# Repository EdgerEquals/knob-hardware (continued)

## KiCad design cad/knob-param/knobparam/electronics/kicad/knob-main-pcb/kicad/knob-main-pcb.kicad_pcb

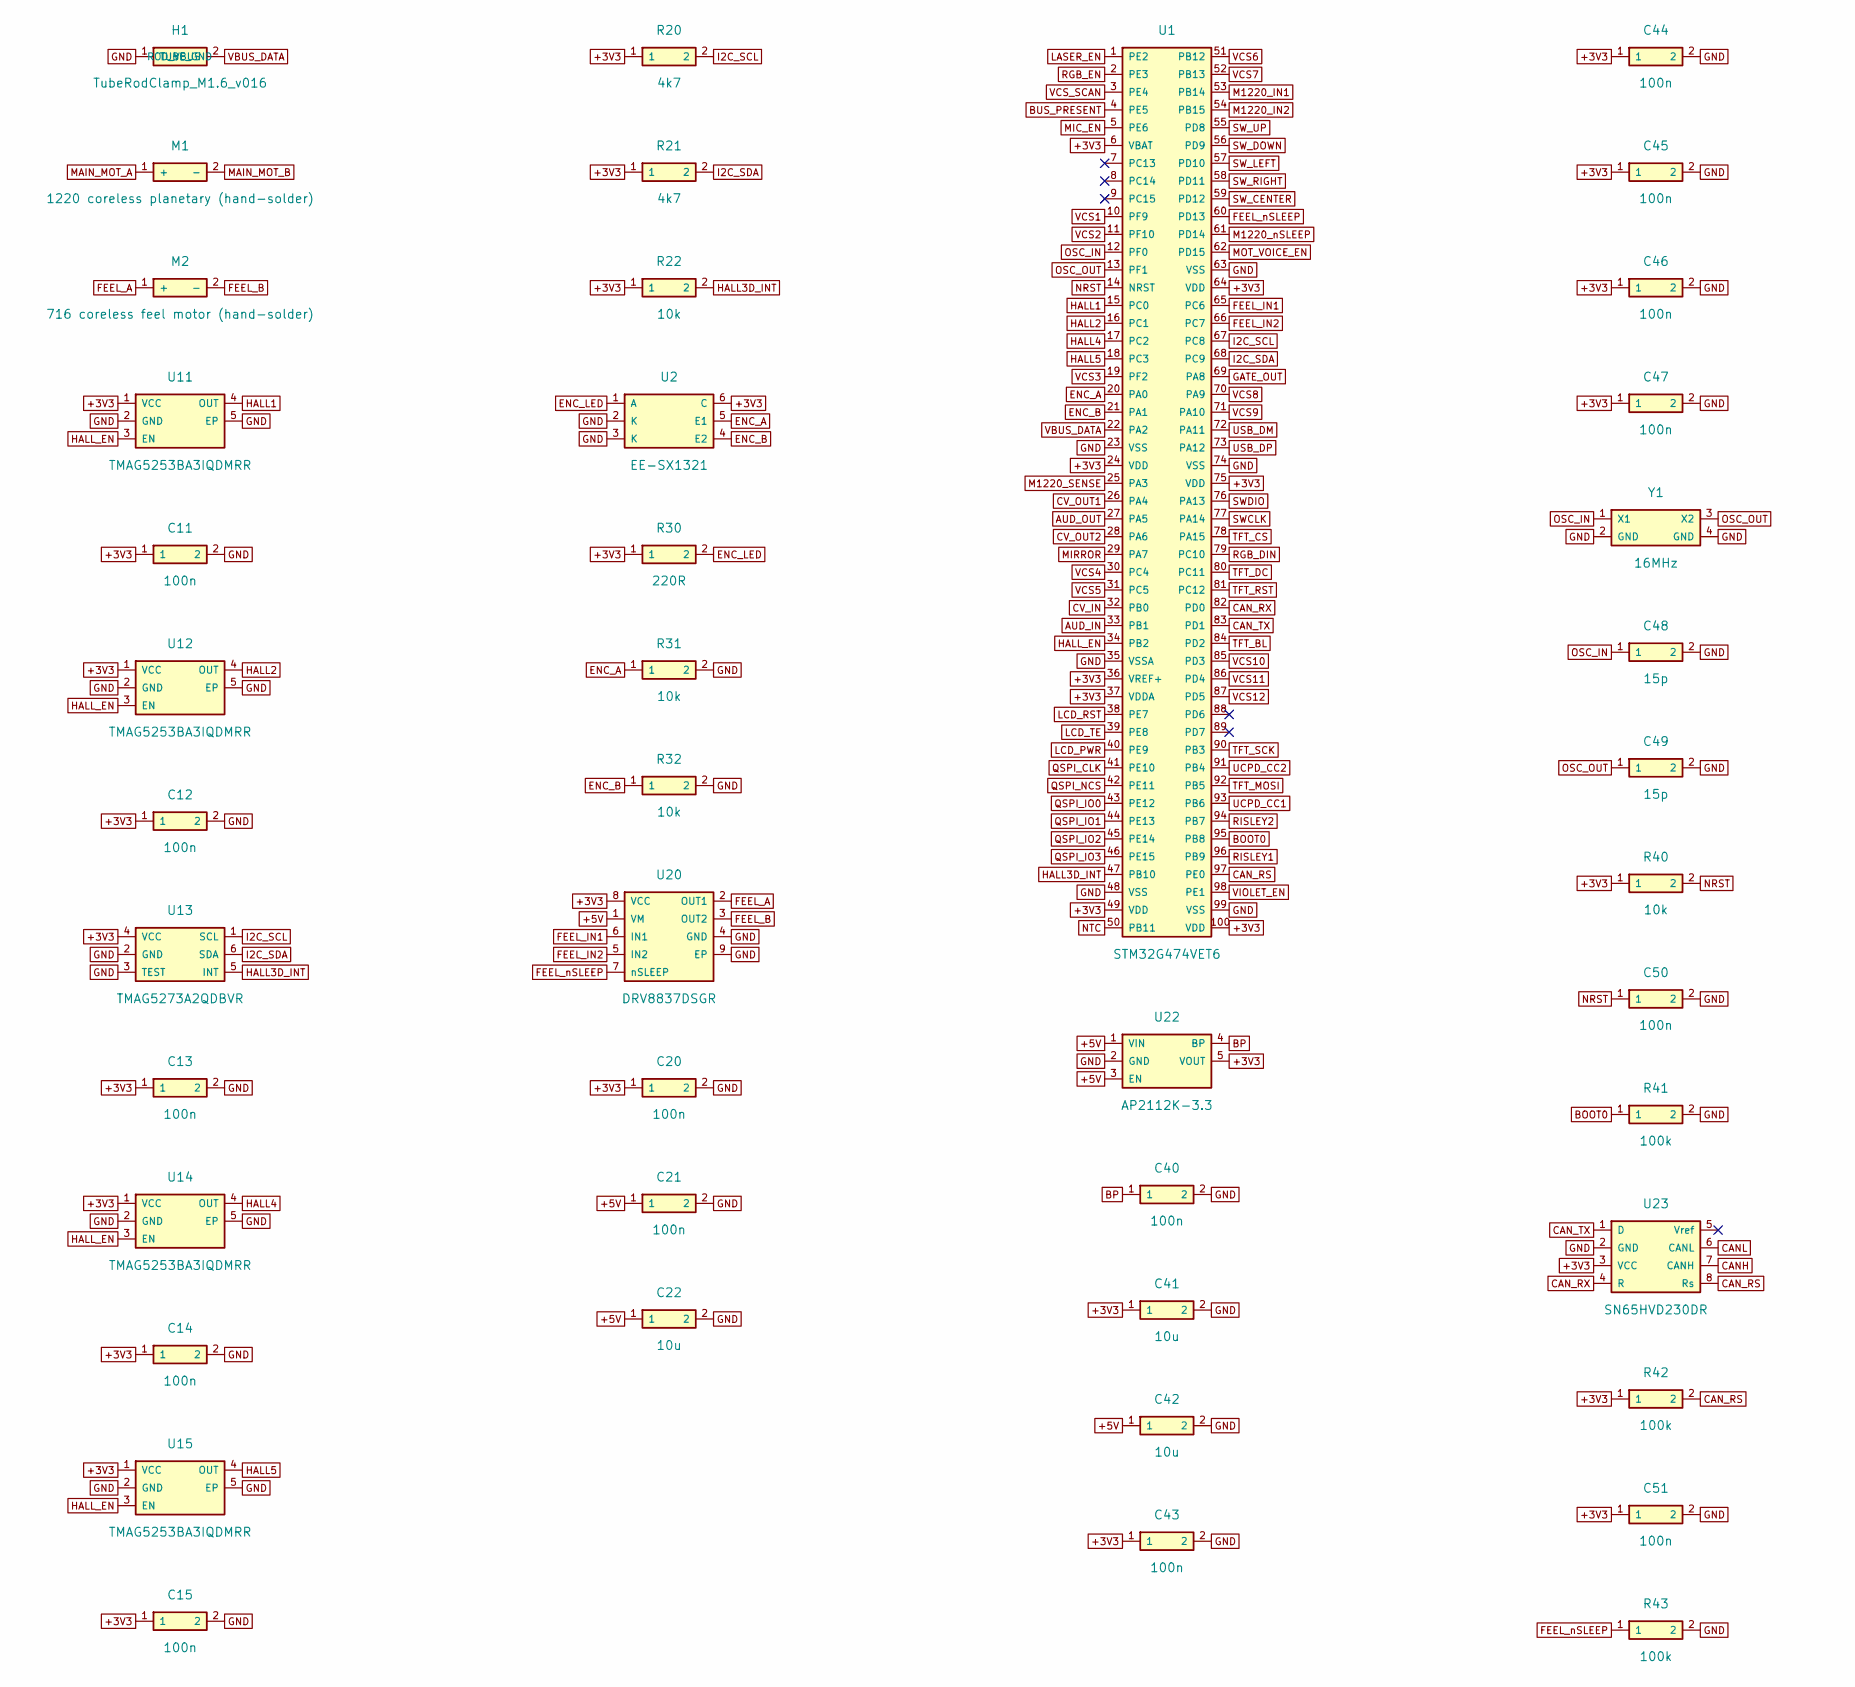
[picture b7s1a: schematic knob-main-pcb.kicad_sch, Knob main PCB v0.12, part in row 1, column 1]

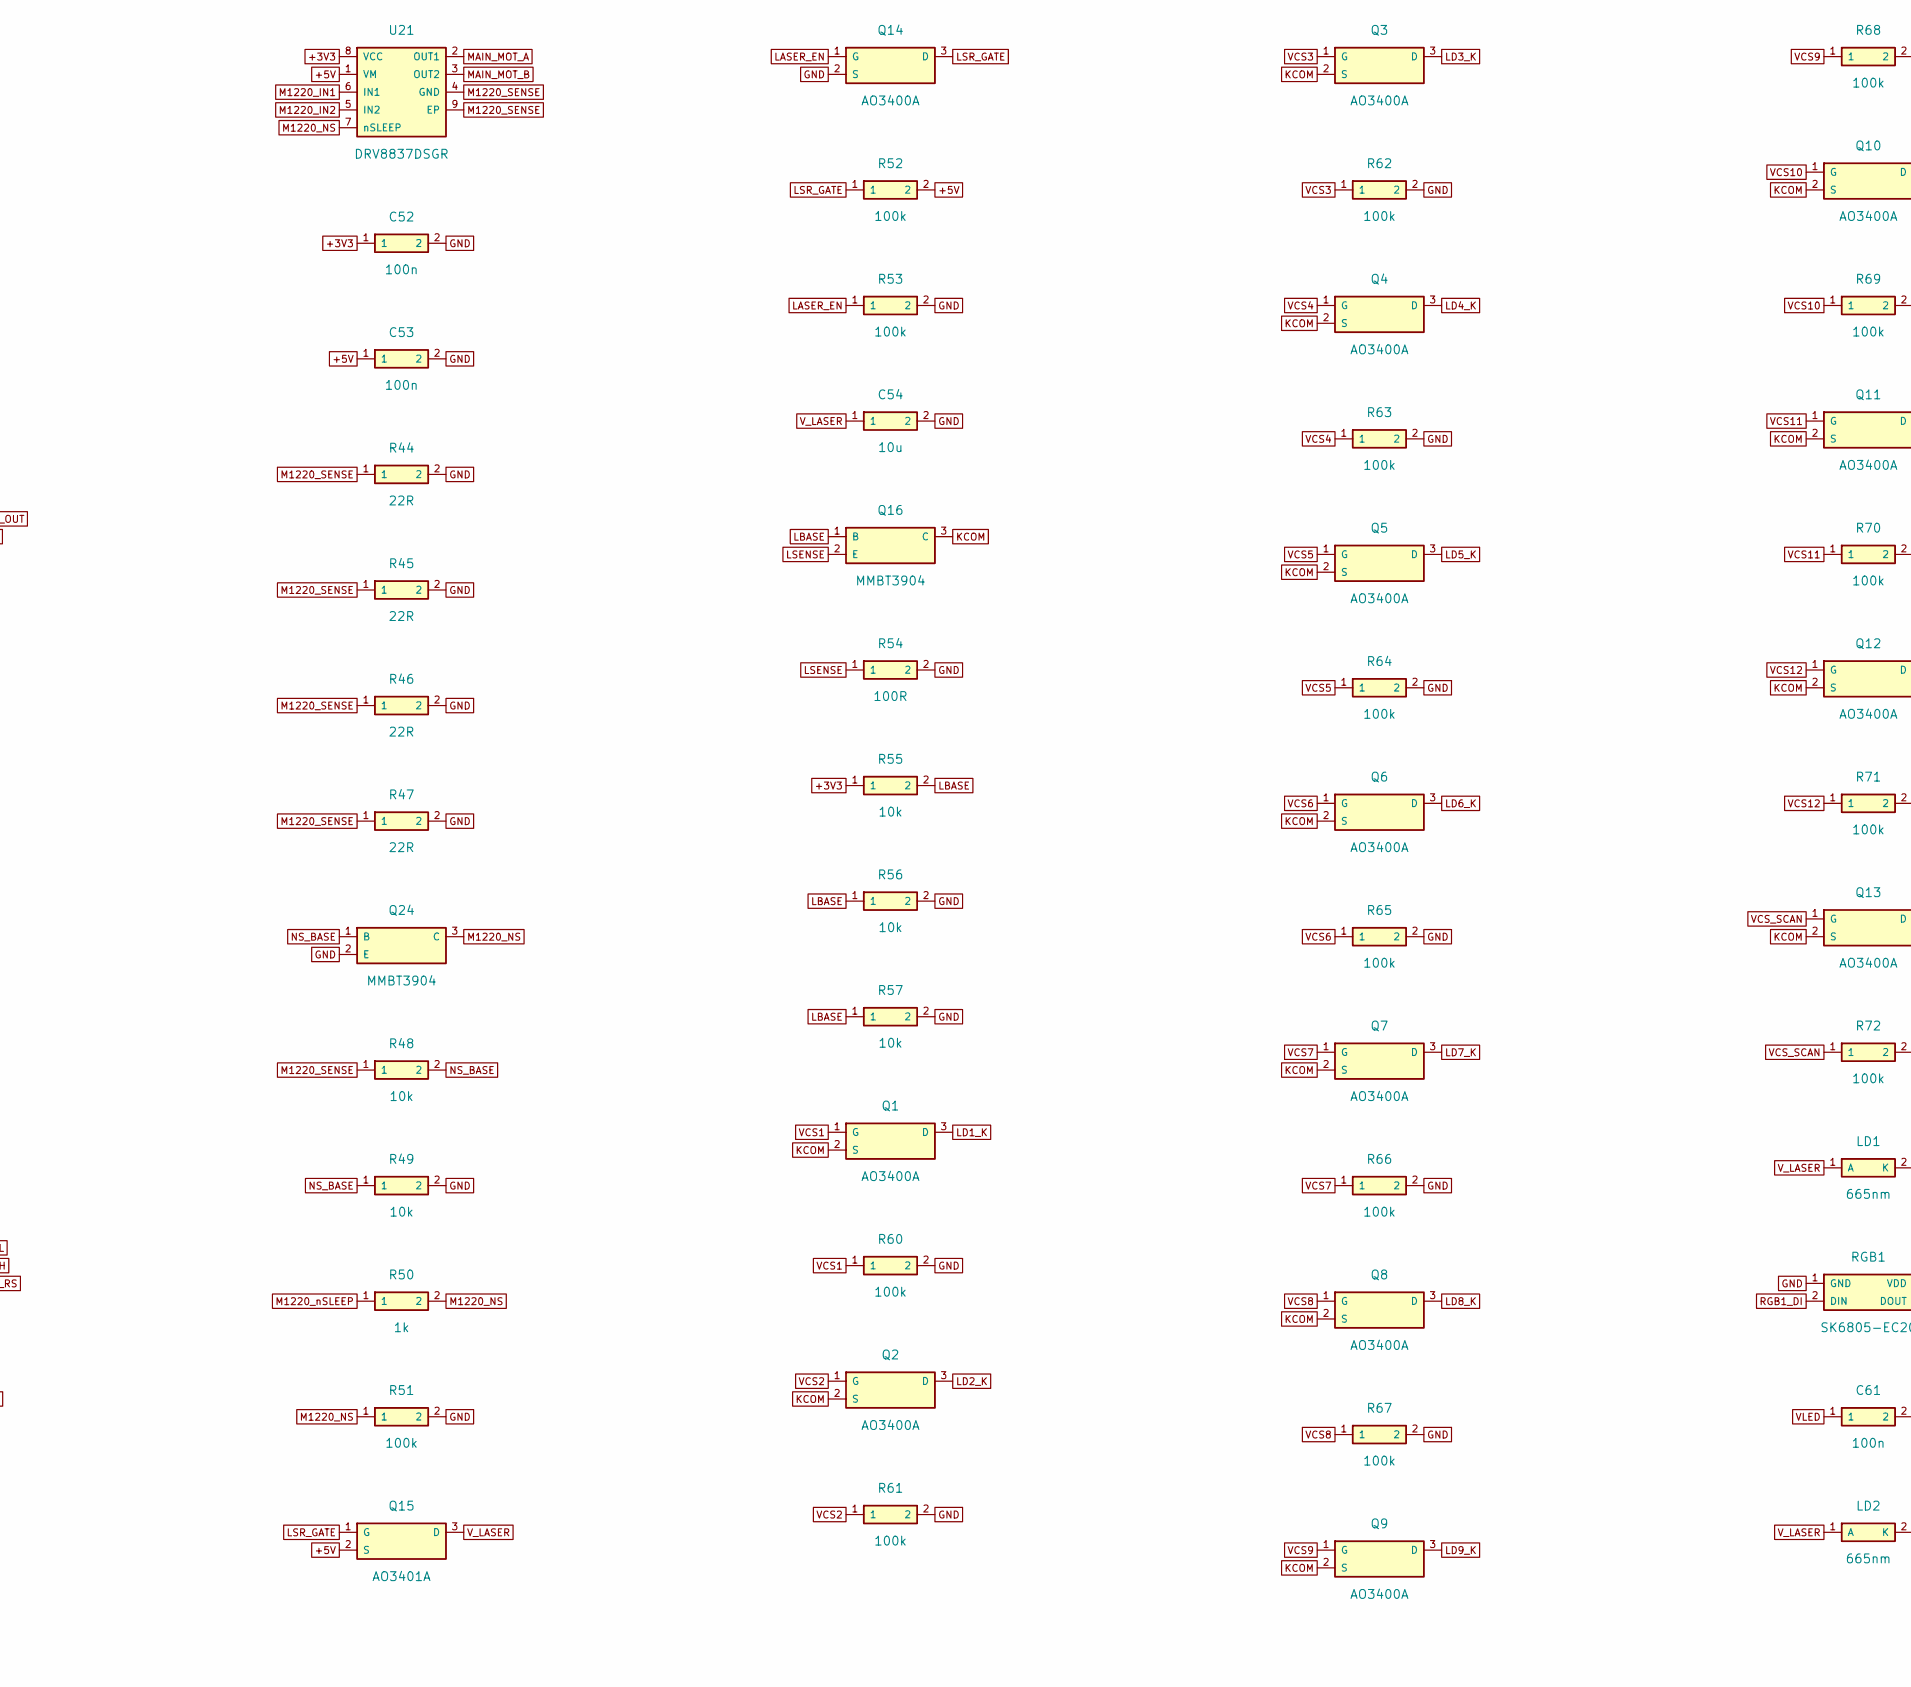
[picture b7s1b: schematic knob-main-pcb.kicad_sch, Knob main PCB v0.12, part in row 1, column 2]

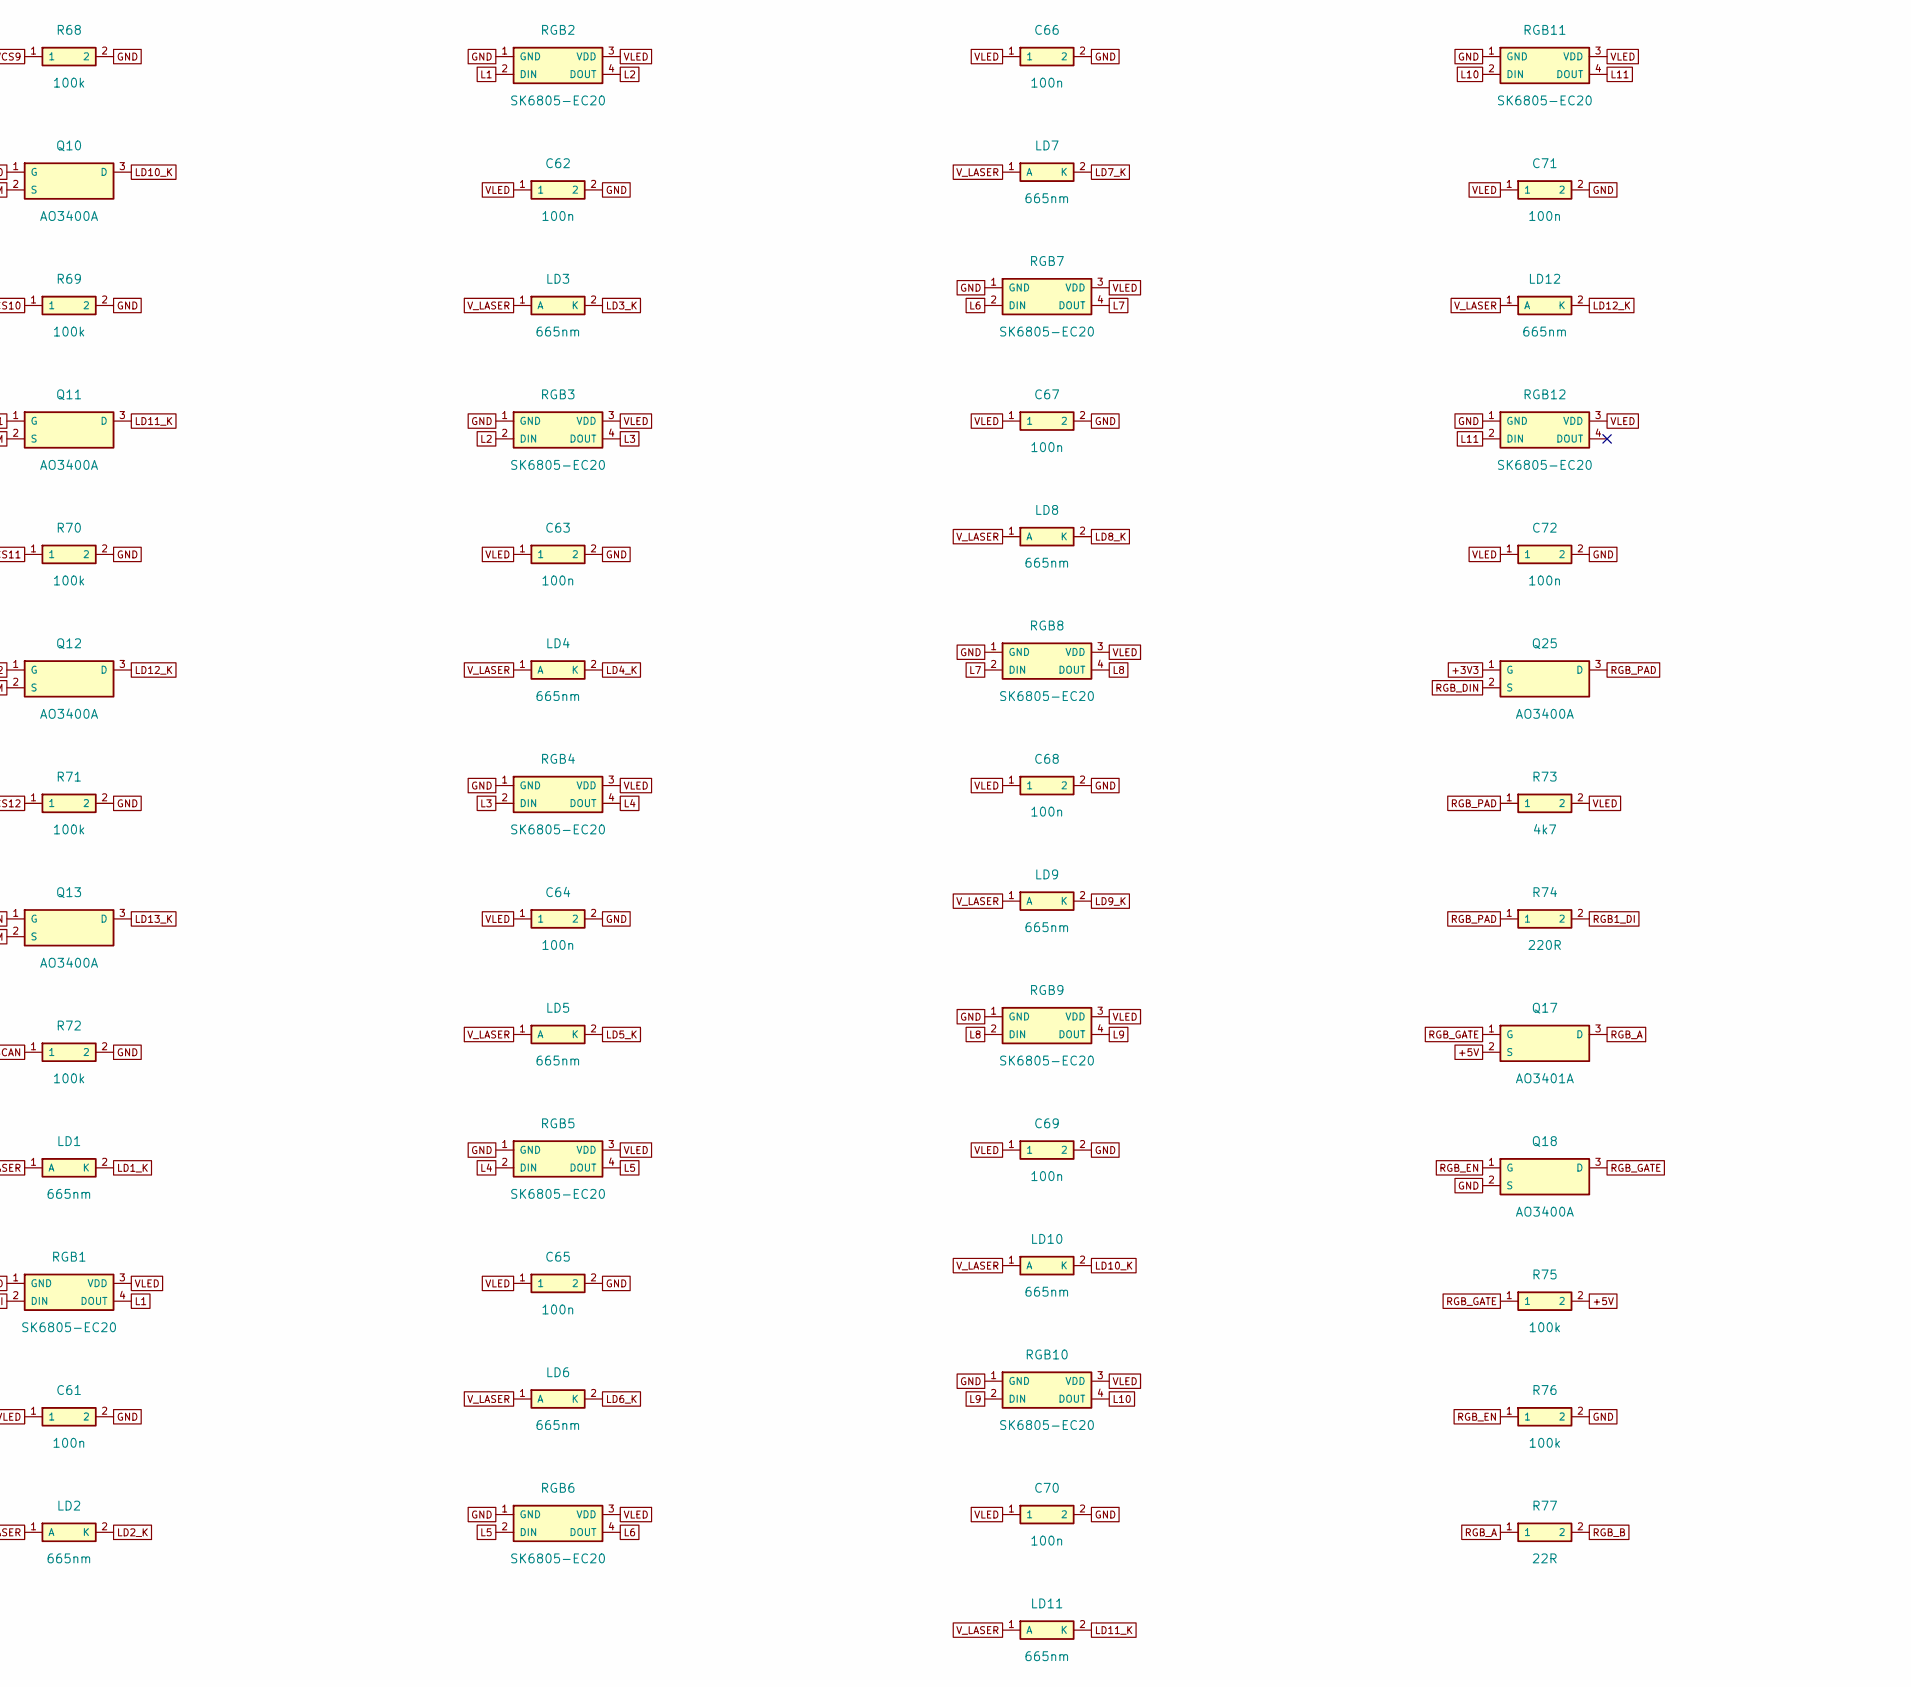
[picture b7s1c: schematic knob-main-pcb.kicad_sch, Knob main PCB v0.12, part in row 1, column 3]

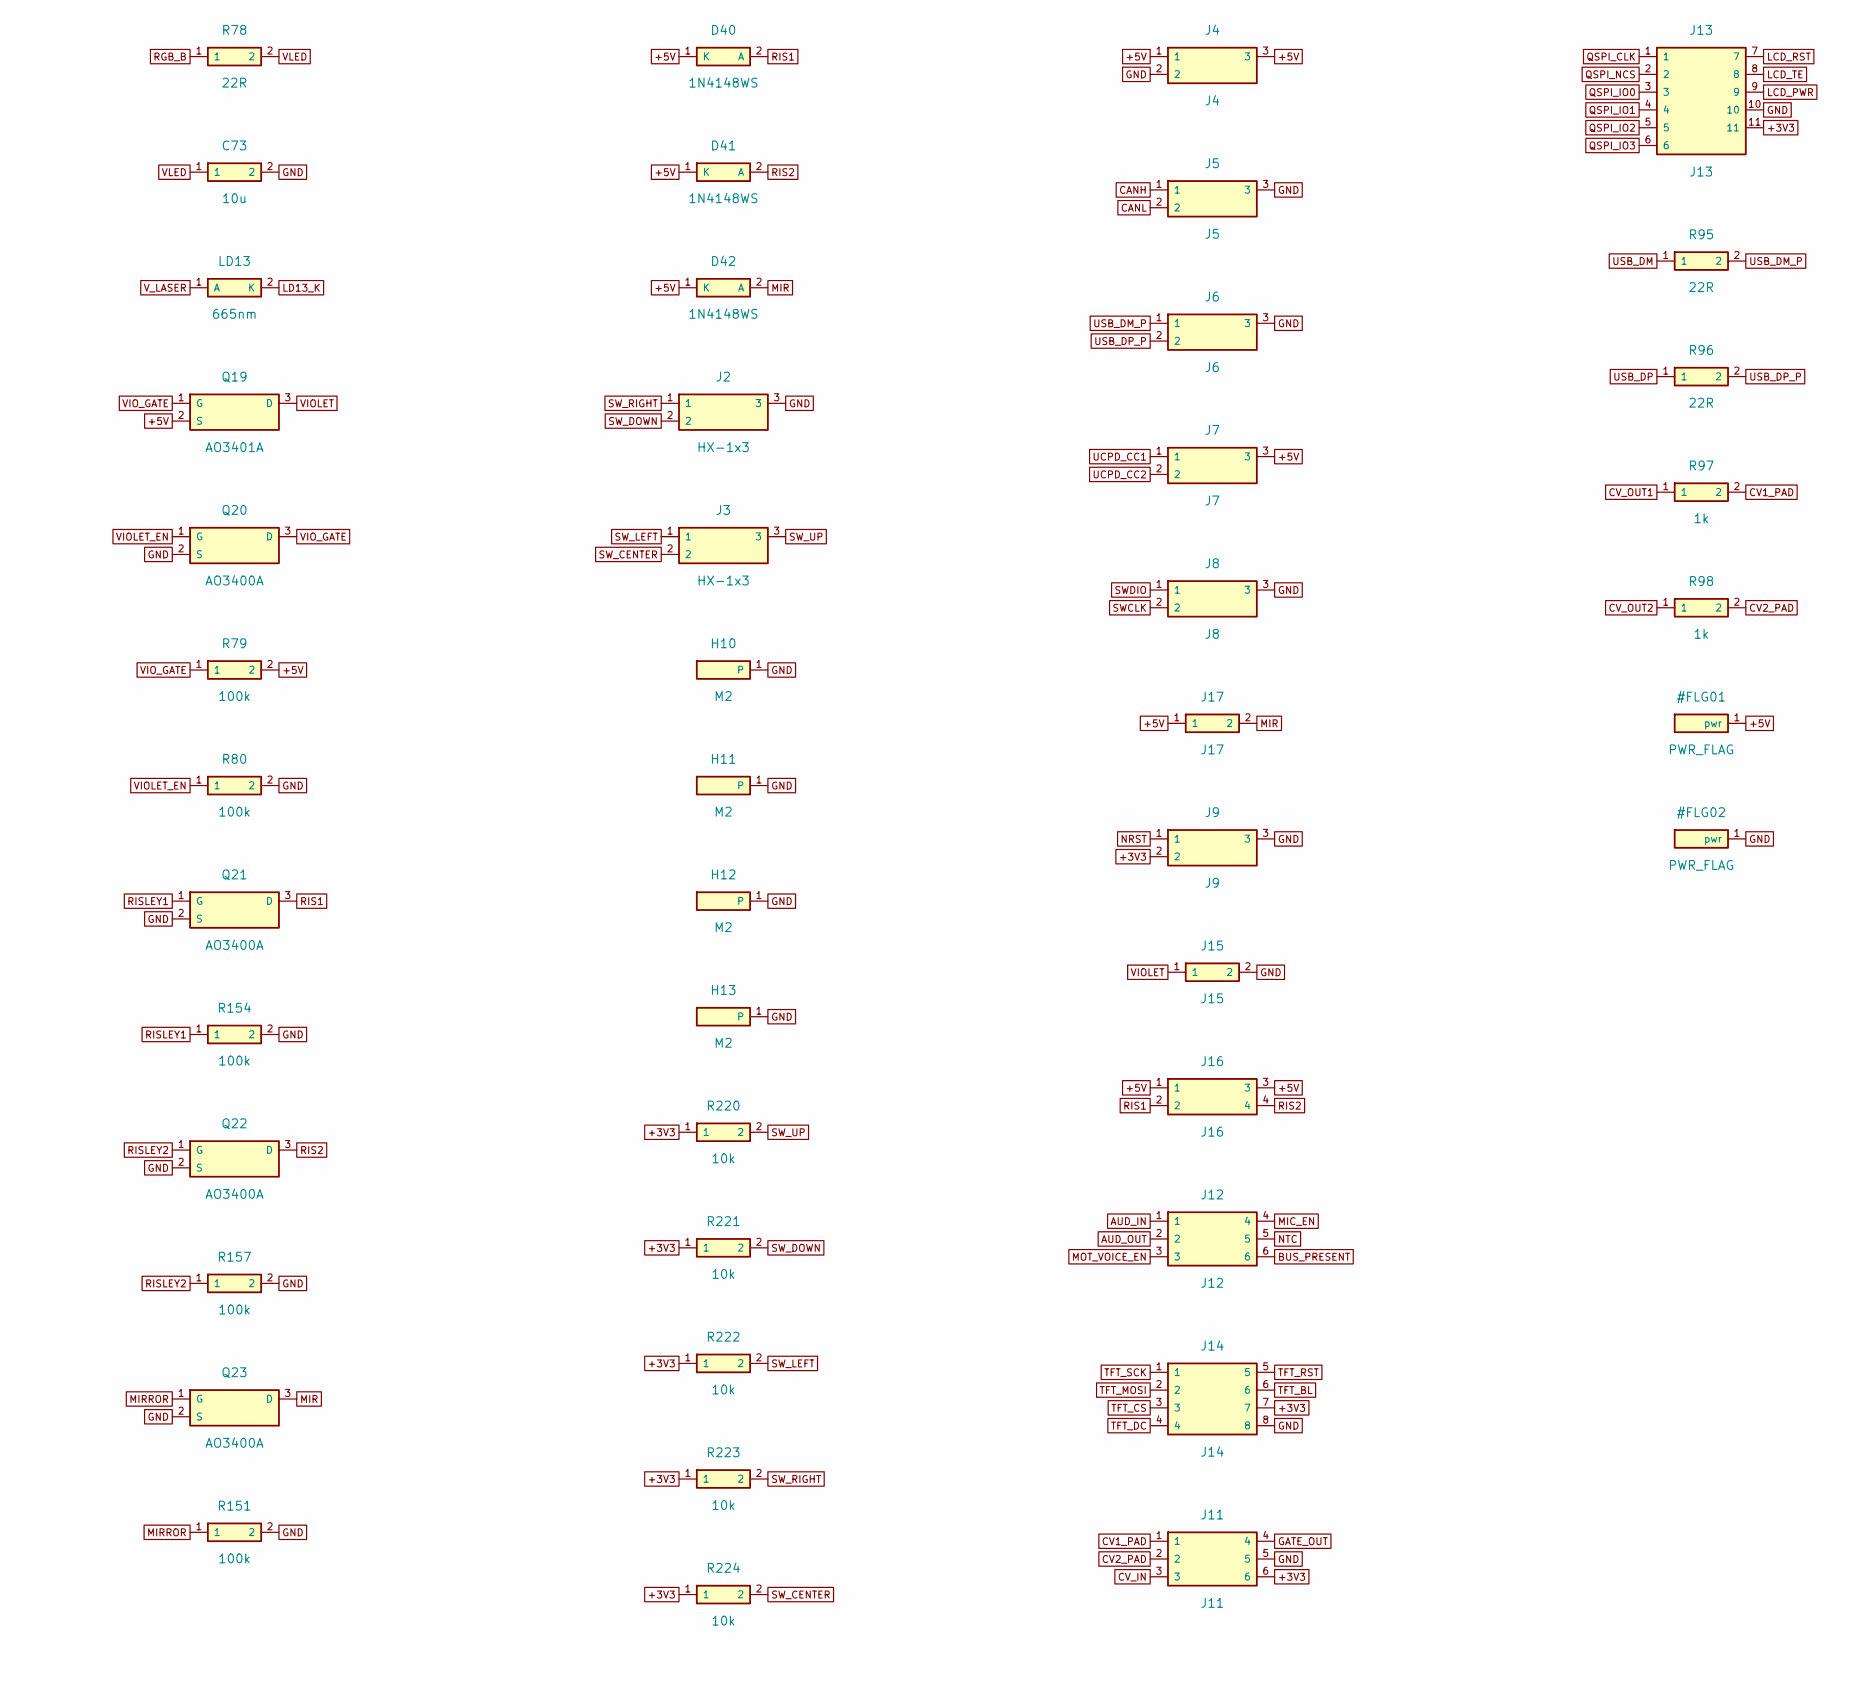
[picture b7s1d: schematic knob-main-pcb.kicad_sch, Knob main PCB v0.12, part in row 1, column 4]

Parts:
C11, C12, C13, C14, C15, C20, C21, C40, C43, C44, C45, C46, C47, C50, C51, C52, C53, C61, C62, C63, C64, C65, C66, C67, C68, C69, C70, C71, C72: 100n; C_0402; MPN CL05B104KO5NNNC; LCSC C1525
C22, C41, C42, C54, C73: 10u; C_0603; MPN CL10A106KP8NNNC; LCSC C19702
C48, C49: 15p; C_0402; MPN 0402CG150J500NT; LCSC C1548
D40, D41, D42: 1N4148WS; D_SOD-323; MPN 1N4148WS; LCSC C2128
H1: TubeRodClamp_M1.6_v016; TubeRodClamp_Main_M1.6_v016
H10, H11, H12, H13: M2; Mount_M2_PTH
J2, J3: HX-1x3; PinSocket_1x03_P2.54; MPN HX PM2.54-1x3P ZC H11; LCSC C41427518
J4: J4; PadRow_1x03
J5: J5; PadRow_1x03
J6: J6; PadRow_1x03
J7: J7; PadRow_1x03
J8: J8; PadRow_1x03
J9: J9; PadRow_1x03
J11: J11; PadRow_1x06
J12: J12; PadRow_1x06
J13: J13; PadRow_1x11
J14: J14; PadRow_1x08
J15: J15; PadRow_1x02
J16: J16; PadRow_1x04
J17: J17; PadRow_1x02
LD1, LD2, LD3, LD4, LD5, LD6, LD7, LD8, LD9, LD10, LD11, LD12, LD13: 665nm; LED_2835_VCSEL; MPN JNJ-V-2835CW-665003-S-D1; LCSC C42375664
M1: 1220 coreless planetary (hand-solder); Motor_1220_Tabs_Relief
M2: 716 coreless feel motor (hand-solder); FeelMotor_716_LeadPads
Q1, Q2, Q3, Q4, Q5, Q6, Q7, Q8, Q9, Q10, Q11, Q12, Q13, Q14, Q18, Q20, Q21, Q22, Q23, Q25: AO3400A; SOT-23; MPN AO3400A; LCSC C20917
Q15, Q17, Q19: AO3401A; SOT-23; MPN AO3401A; LCSC C15127
Q16, Q24: MMBT3904; SOT-23; MPN MMBT3904; LCSC C20526
R20, R21, R73: 4k7; R_0402; MPN 0402WGF4701TCE; LCSC C25900
R22, R31, R32, R40, R48, R49, R55, R56, R57, R220, R221, R222, R223, R224: 10k; R_0402; MPN RC0402FR-0710KL; LCSC C60490
R30, R74: 220R; R_0402; MPN 0402WGF2200TCE; LCSC C25091
R41, R42, R43, R51, R52, R53, R60, R61, R62, R63, R64, R65, R66, R67, R68, R69, R70, R71, R72, R75, R76, R79, R80, R151, R154, R157: 100k; R_0402; MPN 0402WGF1003TCE; LCSC C25741
R44, R45, R46, R47, R77, R78, R95, R96: 22R; R_0402; MPN 0402WGF220KTCE; LCSC C25101
R50, R97, R98: 1k; R_0402; MPN 0402WGF1001TCE; LCSC C11702
R54: 100R; R_0603; MPN 0603WAF1000T5E; LCSC C22775
RGB1, RGB2, RGB3, RGB4, RGB5, RGB6, RGB7, RGB8, RGB9, RGB10, RGB11, RGB12: SK6805-EC20; LED_SK6805_EC20; MPN SK6805-EC20; LCSC C2890036
U1: STM32G474VET6; LQFP-100_14x14mm_P0.5mm; MPN STM32G474VET6; LCSC C431632
U2: EE-SX1321; Omron_EE-SX1321; MPN EE-SX1321; LCSC C469128
U11, U12, U14, U15: TMAG5253BA3IQDMRR; X2SON-4_TMAG5253; MPN TMAG5253BA3IQDMRR; LCSC C22401868
U13: TMAG5273A2QDBVR; SOT-23-6_TMAG5273_Tight; MPN TMAG5273A2QDBVR; LCSC C3715882
U20, U21: DRV8837DSGR; WSON-8_2x2_DRV8837; MPN DRV8837DSGR; LCSC C39159
U22: AP2112K-3.3; SOT-23-5; MPN AP2112K-3.3TRG1; LCSC C51118
U23: SN65HVD230DR; SOIC-8_3.9x4.9mm_P1.27mm; MPN SN65HVD230DR; LCSC C12084
Y1: 16MHz; Crystal_3225; MPN X322516MLB4SI; LCSC C13738

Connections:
+3V3: C11.1, C12.1, C13.1, C14.1, C15.1, C20.1, C41.1, C43.1, C44.1, C45.1, C46.1, C47.1, C51.1, C52.1, J9.2, J11.6, J13.11, J14.7, Q25.1 (G), R20.1, R21.1, R22.1, R30.1, R40.1, R42.1, R55.1, R220.1, R221.1, R222.1, R223.1, R224.1, U1.6 (VBAT), U1.24 (VDD), U1.36 (VREF+), U1.37 (VDDA), U1.49 (VDD), U1.64 (VDD), U1.75 (VDD), U1.100 (VDD), U2.6 (C), U11.1 (VCC), U12.1 (VCC), U13.4 (VCC), U14.1 (VCC), U15.1 (VCC), U20.8 (VCC), U21.8 (VCC), U22.5 (VOUT), U23.3 (VCC)
+5V: C21.1, C22.1, C42.1, C53.1, D40.1 (K), D41.1 (K), D42.1 (K), J4.1, J4.3, J7.3, J16.1, J16.3, J17.1, Q15.2 (S), Q17.2 (S), Q19.2 (S), R52.2, R75.2, R79.2, U20.1 (VM), U21.1 (VM), U22.1 (VIN), U22.3 (EN)
AUD_IN: J12.1, U1.33 (PB1)
AUD_OUT: J12.2, U1.27 (PA5)
BOOT0: R41.1, U1.95 (PB8)
BP: C40.1, U22.4 (BP)
BUS_PRESENT: J12.6, U1.4 (PE5)
CANH: J5.1, U23.7 (CANH)
CANL: J5.2, U23.6 (CANL)
CAN_RS: R42.2, U1.97 (PE0), U23.8 (Rs)
CAN_RX: U1.82 (PD0), U23.4 (R)
CAN_TX: U1.83 (PD1), U23.1 (D)
CV1_PAD: J11.1, R97.2
CV2_PAD: J11.2, R98.2
CV_IN: J11.3, U1.32 (PB0)
CV_OUT1: R97.1, U1.26 (PA4)
CV_OUT2: R98.1, U1.28 (PA6)
ENC_A: R31.1, U1.20 (PA0), U2.5 (E1)
ENC_B: R32.1, U1.21 (PA1), U2.4 (E2)
ENC_LED: R30.2, U2.1 (A)
FEEL_A: M2.1 (+), U20.2 (OUT1)
FEEL_B: M2.2 (-), U20.3 (OUT2)
FEEL_IN1: U1.65 (PC6), U20.6 (IN1)
FEEL_IN2: U1.66 (PC7), U20.5 (IN2)
FEEL_nSLEEP: R43.1, U1.60 (PD13), U20.7 (nSLEEP)
GATE_OUT: J11.4, U1.69 (PA8)
GND: C11.2, C12.2, C13.2, C14.2, C15.2, C20.2, C21.2, C22.2, C40.2, C41.2, C42.2, C43.2, C44.2, C45.2, C46.2, C47.2, C48.2, C49.2, C50.2, C51.2, C52.2, C53.2, C54.2, C61.2, C62.2, C63.2, C64.2, C65.2, C66.2, C67.2, C68.2, C69.2, C70.2, C71.2, C72.2, C73.2, H1.1 (TUBE_GND), H10.1, H11.1, H12.1, H13.1, J2.3, J4.2, J5.3, J6.3, J8.3, J9.3, J11.5, J13.10, J14.8, J15.2, Q14.2 (S), Q18.2 (S), Q20.2 (S), Q21.2 (S), Q22.2 (S), Q23.2 (S), Q24.2 (E), R31.2, R32.2, R41.2, R43.2, R44.2, R45.2, R46.2, R47.2, R49.2, R51.2, R53.2, R54.2, R56.2, R57.2, R60.2, R61.2, R62.2, R63.2, R64.2, R65.2, R66.2, R67.2, R68.2, R69.2, R70.2, R71.2, R72.2, R76.2, R80.2, R151.2, R154.2, R157.2, RGB1.1 (GND), RGB2.1 (GND), RGB3.1 (GND), RGB4.1 (GND), RGB5.1 (GND), RGB6.1 (GND), RGB7.1 (GND), RGB8.1 (GND), RGB9.1 (GND), RGB10.1 (GND), RGB11.1 (GND), RGB12.1 (GND), U1.23 (VSS), U1.35 (VSSA), U1.48 (VSS), U1.63 (VSS), U1.74 (VSS), U1.99 (VSS), U2.2 (K), U2.3 (K), U11.2 (GND), U11.5 (EP), U12.2 (GND), U12.5 (EP), U13.2 (GND), U13.3 (TEST), U14.2 (GND), U14.5 (EP), U15.2 (GND), U15.5 (EP), U20.4 (GND), U20.9 (EP), U22.2 (GND), U23.2 (GND), Y1.2 (GND), Y1.4 (GND)
HALL1: U1.15 (PC0), U11.4 (OUT)
HALL2: U1.16 (PC1), U12.4 (OUT)
HALL3D_INT: R22.2, U1.47 (PB10), U13.5 (INT)
HALL4: U1.17 (PC2), U14.4 (OUT)
HALL5: U1.18 (PC3), U15.4 (OUT)
HALL_EN: U1.34 (PB2), U11.3 (EN), U12.3 (EN), U14.3 (EN), U15.3 (EN)
I2C_SCL: R20.2, U1.67 (PC8), U13.1 (SCL)
I2C_SDA: R21.2, U1.68 (PC9), U13.6 (SDA)
KCOM: Q1.2 (S), Q2.2 (S), Q3.2 (S), Q4.2 (S), Q5.2 (S), Q6.2 (S), Q7.2 (S), Q8.2 (S), Q9.2 (S), Q10.2 (S), Q11.2 (S), Q12.2 (S), Q13.2 (S), Q16.3 (C)
L1: RGB1.4 (DOUT), RGB2.2 (DIN)
L2: RGB2.4 (DOUT), RGB3.2 (DIN)
L3: RGB3.4 (DOUT), RGB4.2 (DIN)
L4: RGB4.4 (DOUT), RGB5.2 (DIN)
L5: RGB5.4 (DOUT), RGB6.2 (DIN)
L6: RGB6.4 (DOUT), RGB7.2 (DIN)
L7: RGB7.4 (DOUT), RGB8.2 (DIN)
L8: RGB8.4 (DOUT), RGB9.2 (DIN)
L9: RGB9.4 (DOUT), RGB10.2 (DIN)
L10: RGB10.4 (DOUT), RGB11.2 (DIN)
L11: RGB11.4 (DOUT), RGB12.2 (DIN)
LASER_EN: Q14.1 (G), R53.1, U1.1 (PE2)
LBASE: Q16.1 (B), R55.2, R56.1, R57.1
LCD_PWR: J13.9, U1.40 (PE9)
LCD_RST: J13.7, U1.38 (PE7)
LCD_TE: J13.8, U1.39 (PE8)
LD1_K: LD1.2 (K), Q1.3 (D)
LD2_K: LD2.2 (K), Q2.3 (D)
LD3_K: LD3.2 (K), Q3.3 (D)
LD4_K: LD4.2 (K), Q4.3 (D)
LD5_K: LD5.2 (K), Q5.3 (D)
LD6_K: LD6.2 (K), Q6.3 (D)
LD7_K: LD7.2 (K), Q7.3 (D)
LD8_K: LD8.2 (K), Q8.3 (D)
LD9_K: LD9.2 (K), Q9.3 (D)
LD10_K: LD10.2 (K), Q10.3 (D)
LD11_K: LD11.2 (K), Q11.3 (D)
LD12_K: LD12.2 (K), Q12.3 (D)
LD13_K: LD13.2 (K), Q13.3 (D)
LSENSE: Q16.2 (E), R54.1
LSR_GATE: Q14.3 (D), Q15.1 (G), R52.1
M1220_IN1: U1.53 (PB14), U21.6 (IN1)
M1220_IN2: U1.54 (PB15), U21.5 (IN2)
M1220_NS: Q24.3 (C), R50.2, R51.1, U21.7 (nSLEEP)
M1220_SENSE: R44.1, R45.1, R46.1, R47.1, R48.1, U1.25 (PA3), U21.4 (GND), U21.9 (EP)
M1220_nSLEEP: R50.1, U1.61 (PD14)
MAIN_MOT_A: M1.1 (+), U21.2 (OUT1)
MAIN_MOT_B: M1.2 (-), U21.3 (OUT2)
MIC_EN: J12.4, U1.5 (PE6)
MIR: D42.2 (A), J17.2, Q23.3 (D)
MIRROR: Q23.1 (G), R151.1, U1.29 (PA7)
MOT_VOICE_EN: J12.3, U1.62 (PD15)
NRST: C50.1, J9.1, R40.2, U1.14 (NRST)
NS_BASE: Q24.1 (B), R48.2, R49.1
NTC: J12.5, U1.50 (PB11)
OSC_IN: C48.1, U1.12 (PF0), Y1.1 (X1)
OSC_OUT: C49.1, U1.13 (PF1), Y1.3 (X2)
QSPI_CLK: J13.1, U1.41 (PE10)
QSPI_IO0: J13.3, U1.43 (PE12)
QSPI_IO1: J13.4, U1.44 (PE13)
QSPI_IO2: J13.5, U1.45 (PE14)
QSPI_IO3: J13.6, U1.46 (PE15)
QSPI_NCS: J13.2, U1.42 (PE11)
RGB1_DI: R74.2, RGB1.2 (DIN)
RGB_A: Q17.3 (D), R77.1
RGB_B: R77.2, R78.1
RGB_DIN: Q25.2 (S), U1.79 (PC10)
RGB_EN: Q18.1 (G), R76.1, U1.2 (PE3)
RGB_GATE: Q17.1 (G), Q18.3 (D), R75.1
RGB_PAD: Q25.3 (D), R73.1, R74.1
RIS1: D40.2 (A), J16.2, Q21.3 (D)
RIS2: D41.2 (A), J16.4, Q22.3 (D)
RISLEY1: Q21.1 (G), R154.1, U1.96 (PB9)
RISLEY2: Q22.1 (G), R157.1, U1.94 (PB7)
SWCLK: J8.2, U1.77 (PA14)
SWDIO: J8.1, U1.76 (PA13)
SW_CENTER: J3.2, R224.2, U1.59 (PD12)
SW_DOWN: J2.2, R221.2, U1.56 (PD9)
SW_LEFT: J3.1, R222.2, U1.57 (PD10)
SW_RIGHT: J2.1, R223.2, U1.58 (PD11)
SW_UP: J3.3, R220.2, U1.55 (PD8)
TFT_BL: J14.6, U1.84 (PD2)
TFT_CS: J14.3, U1.78 (PA15)
TFT_DC: J14.4, U1.80 (PC11)
TFT_MOSI: J14.2, U1.92 (PB5)
TFT_RST: J14.5, U1.81 (PC12)
TFT_SCK: J14.1, U1.90 (PB3)
UCPD_CC1: J7.1, U1.93 (PB6)
UCPD_CC2: J7.2, U1.91 (PB4)
USB_DM: R95.1, U1.72 (PA11)
USB_DM_P: J6.1, R95.2
USB_DP: R96.1, U1.73 (PA12)
USB_DP_P: J6.2, R96.2
VBUS_DATA: H1.2 (ROD_VBUS), U1.22 (PA2)
VCS1: Q1.1 (G), R60.1, U1.10 (PF9)
VCS2: Q2.1 (G), R61.1, U1.11 (PF10)
VCS3: Q3.1 (G), R62.1, U1.19 (PF2)
VCS4: Q4.1 (G), R63.1, U1.30 (PC4)
VCS5: Q5.1 (G), R64.1, U1.31 (PC5)
VCS6: Q6.1 (G), R65.1, U1.51 (PB12)
VCS7: Q7.1 (G), R66.1, U1.52 (PB13)
VCS8: Q8.1 (G), R67.1, U1.70 (PA9)
VCS9: Q9.1 (G), R68.1, U1.71 (PA10)
VCS10: Q10.1 (G), R69.1, U1.85 (PD3)
VCS11: Q11.1 (G), R70.1, U1.86 (PD4)
VCS12: Q12.1 (G), R71.1, U1.87 (PD5)
VCS_SCAN: Q13.1 (G), R72.1, U1.3 (PE4)
VIOLET: J15.1, Q19.3 (D)
VIOLET_EN: Q20.1 (G), R80.1, U1.98 (PE1)
VIO_GATE: Q19.1 (G), Q20.3 (D), R79.1
VLED: C61.1, C62.1, C63.1, C64.1, C65.1, C66.1, C67.1, C68.1, C69.1, C70.1, C71.1, C72.1, C73.1, R73.2, R78.2, RGB1.3 (VDD), RGB2.3 (VDD), RGB3.3 (VDD), RGB4.3 (VDD), RGB5.3 (VDD), RGB6.3 (VDD), RGB7.3 (VDD), RGB8.3 (VDD), RGB9.3 (VDD), RGB10.3 (VDD), RGB11.3 (VDD), RGB12.3 (VDD)
V_LASER: C54.1, LD1.1 (A), LD2.1 (A), LD3.1 (A), LD4.1 (A), LD5.1 (A), LD6.1 (A), LD7.1 (A), LD8.1 (A), LD9.1 (A), LD10.1 (A), LD11.1 (A), LD12.1 (A), LD13.1 (A), Q15.3 (D)

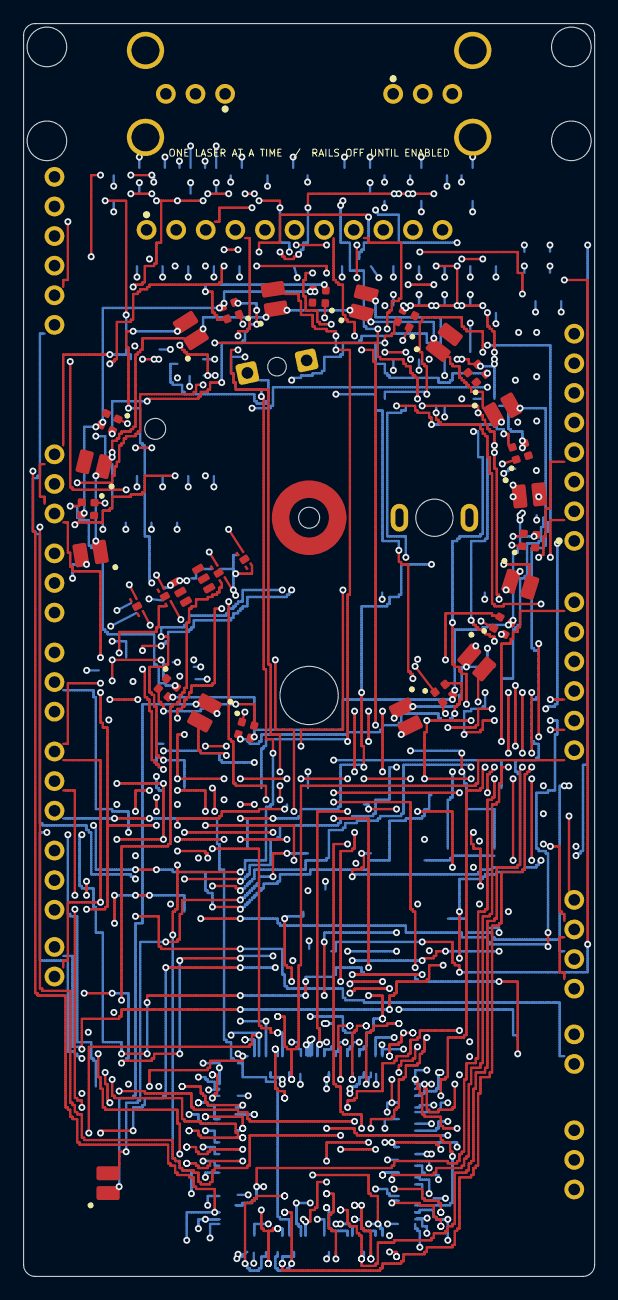
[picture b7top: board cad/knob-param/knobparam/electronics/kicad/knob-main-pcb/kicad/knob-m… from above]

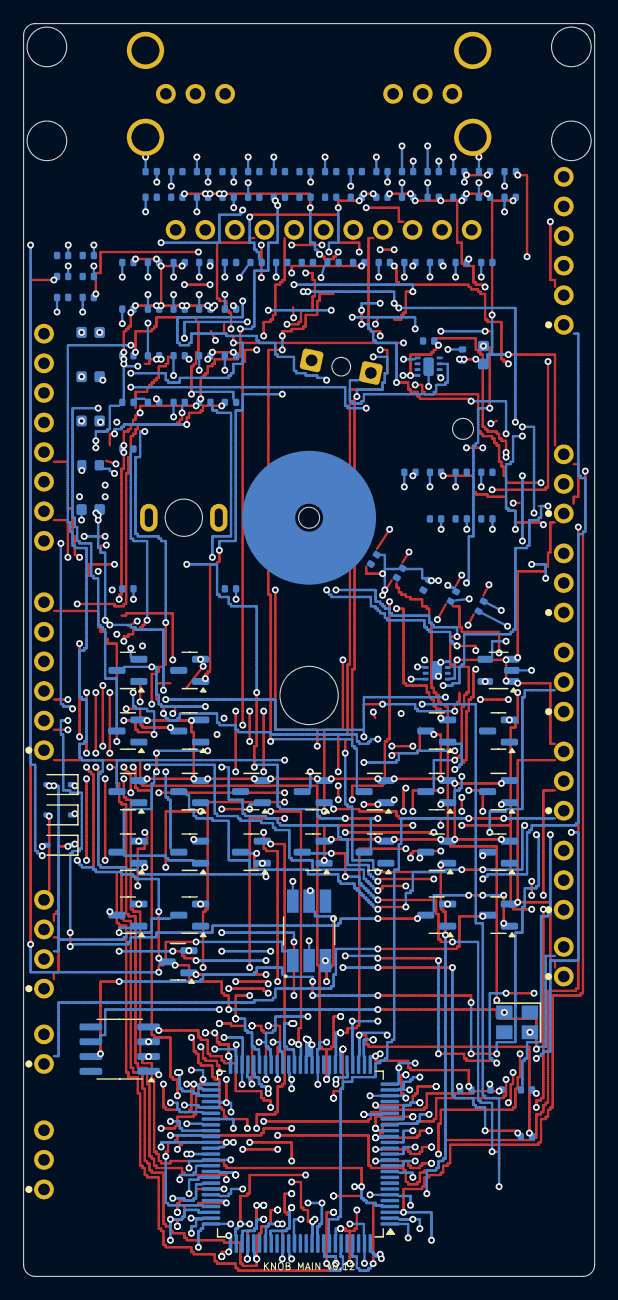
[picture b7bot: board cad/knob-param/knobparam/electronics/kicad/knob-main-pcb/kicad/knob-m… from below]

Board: 4 copper layers, 49.0 x 107.5 mm, 188 parts (140 on the bottom side), 138 nets.

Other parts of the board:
H2: Bearing_F682ZZ_Press_NPTH_5.0mm
H3: Hole_NPTH_1.6
H4: Hole_NPTH_1.8
HS1, HS2, HS3, HS4: Hole_NPTH_3.4
S1: SLOT; Slot_FPC_v04

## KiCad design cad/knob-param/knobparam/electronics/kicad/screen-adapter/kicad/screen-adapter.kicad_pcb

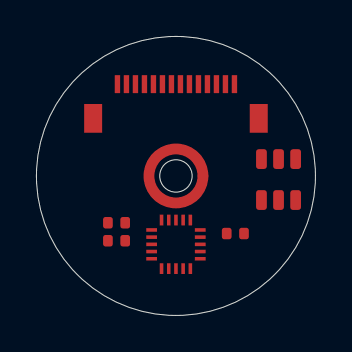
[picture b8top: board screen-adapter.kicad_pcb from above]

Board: 2 copper layers, 15.5 x 15.5 mm, 7 parts (0 on the bottom side), 5 nets, no tracks yet.

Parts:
C1: TubeRodClamp_Adapter_M1.6
C2: 100n; C_0402
J1: FPC_14P_0.5mm_Top
R1, R2: 4k7; R_0402
U1: CH32V003F4U6; QFN-20_3x3_P0.4_CH32V003
U3: TMAG5273A1; SOT-23-6_TMAG5273

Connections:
GND: C1.1, C2.2, U1.4, U3.2, U3.3
HALL_INT: U1.10, U3.5
SCL: R2.2, U1.9, U3.1
SDA: R1.2, U1.8, U3.6
VCC: C2.1, R1.1, R2.1, U1.6, U3.4
